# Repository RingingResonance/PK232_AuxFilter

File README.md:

# PK232_AuxFilter
An added filter stage for the PK232's packet modem descriminator based on the same circuit's existing filter design.

I don't have the best understanding of how this type of filter works so I copied that part of the schematic resistor-per-resistor
with the goal of helping the PK232 perform a little better when the incoming signal isn't full-quieting. Obviously this is for
models that don't have the DSP filter. This filter should be able to be used for other things by changing the resistor and capacitor
values to fit your needs. It would probably work on other TNC's.

Current resistor and capacitor values for Mark/Space:
VHF mode: 1200/2400 hz
HF mode: 2110/2310 hz

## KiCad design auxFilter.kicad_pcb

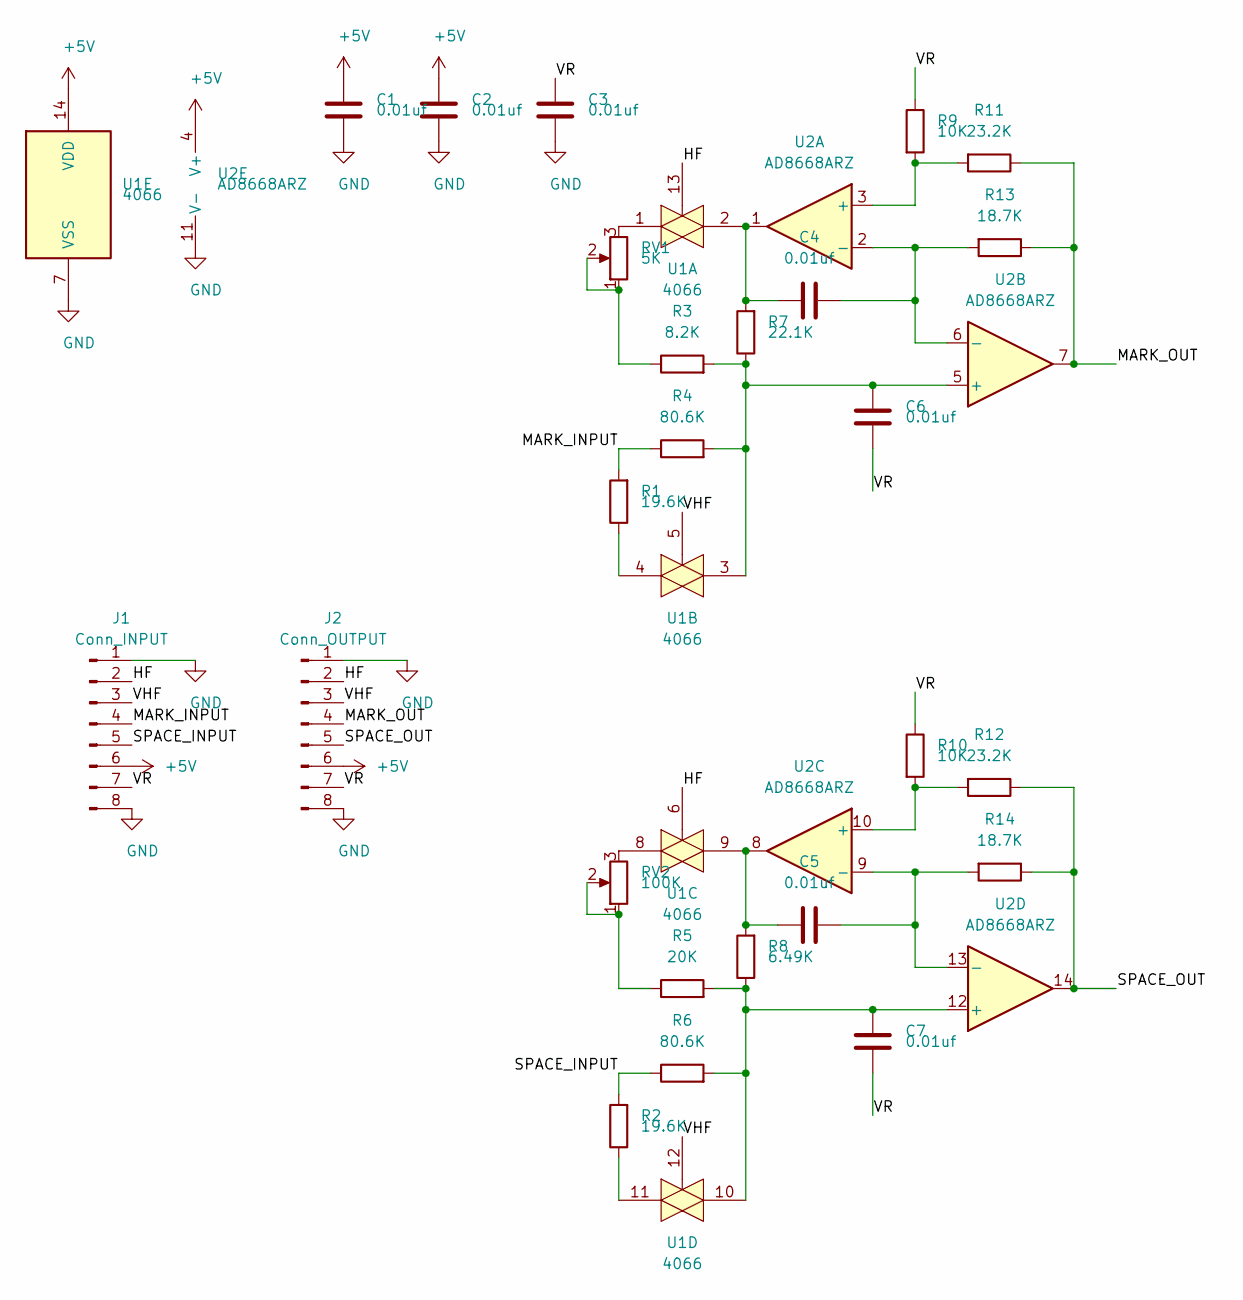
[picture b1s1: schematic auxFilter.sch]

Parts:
C1, C2, C3, C4, C5, C6, C7: 0.01uf; C_0603_HandSoldering; digikey 399-17568-1-ND
J1: Conn_INPUT; Pin_Header_Straight_1x08_Pitch2.54mm
J2: Conn_OUTPUT; Pin_Header_Straight_1x08_Pitch2.54mm
R1, R2: 19.6K; R_0603_HandSoldering; digikey 311-19.6KHRCT-ND
R3: 8.2K; R_0603_HandSoldering; digikey 311-8.2KGRCT-ND
R4, R6: 80.6K; R_0603_HandSoldering; digikey 311-80.6KHRCT-ND
R5: 20K; R_0603_HandSoldering; digikey 13-RC0603FR-1320KLCT-ND
R7: 22.1K; R_0603_HandSoldering; digikey 311-22.1KHRCT-ND
R8: 6.49K; R_0603_HandSoldering; digikey 311-6.49KHRCT-ND
R9, R10: 10K; R_0603_HandSoldering; digikey RNCP0603FTD10K0CT-ND
R11, R12: 23.2K; R_0603_HandSoldering; digikey 311-23.2KHRCT-ND
R13, R14: 18.7K; R_0603_HandSoldering; digikey 311-18.7KHRCT-ND
RV1: 5K; Potentiometer_Trimmer_Vishay_TS53YJ; digikey 3314J-502ECT-ND
RV2: 100K; Potentiometer_Trimmer_Vishay_TS53YJ; digikey 563-ST4ETA104CT-ND
U1: 4066; SOIC-14_3.9x8.7mm_Pitch1.27mm; digikey MC14066BDR2GOSCT-ND
U2: AD8668ARZ; SOIC-14_3.9x8.7mm_Pitch1.27mm; digikey 505-AD8668ARZ-ND

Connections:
+5V: C1.1, C2.1, J1.6, J2.6, U1.14 (VDD), U2.4 (V+)
/HF: J1.2, J2.2, U1.6, U1.13
/MARK_INPUT: J1.4, R1.2, R4.1
/MARK_OUT: J2.4, R11.1, R13.1, U2.7
/SPACE_INPUT: J1.5, R2.2, R6.1
/SPACE_OUT: J2.5, R12.1, R14.1, U2.14
/VHF: J1.3, J2.3, U1.5, U1.12
/VR: C3.1, C6.2, C7.2, J1.7, J2.7, R9.1, R10.1
GND: C1.2, C2.2, C3.2, J1.1, J1.8, J2.1, J2.8, U1.7 (VSS), U2.11 (V-)
unnamed: C4.1, R13.2, U2.2 (-), U2.6 (-)
unnamed: C4.2, R7.2, U1.2, U2.1
unnamed: C5.1, R14.2, U2.9 (-), U2.13 (-)
unnamed: C5.2, R8.2, U1.9, U2.8
unnamed: C6.1, R3.2, R4.2, R7.1, U1.3, U2.5 (+)
unnamed: C7.1, R5.2, R6.2, R8.1, U1.10, U2.12 (+)
unnamed: R1.1, U1.4
unnamed: R2.1, U1.11
unnamed: R3.1, RV1.1, RV1.2
unnamed: R5.1, RV2.1, RV2.2
unnamed: R10.2, R12.2, U2.10 (+)
unnamed: R9.2, R11.2, U2.3 (+)
unnamed: RV1.3, U1.1
unnamed: RV2.3, U1.8

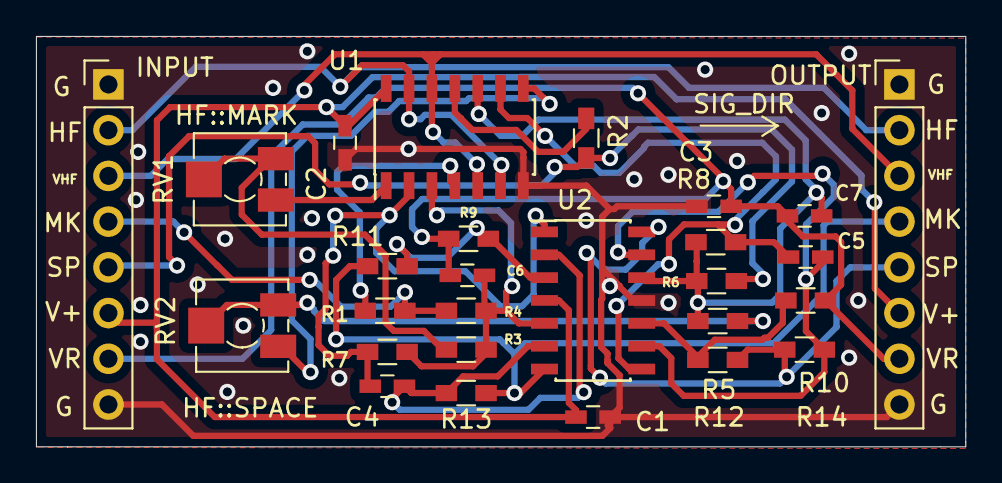
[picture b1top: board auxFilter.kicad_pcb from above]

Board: 2 copper layers, 51.6 x 22.8 mm, 27 parts (0 on the bottom side), 23 nets.

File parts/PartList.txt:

7: 0.01uF 0603 capacitor :: 399-17568-1-ND

2: 19.6K 0603 resistor :: 311-19.6KHRCT-ND

1: 8.2K 0603 resistor :: 311-8.2KGRCT-ND

2: 80.6K 0603 resistor :: 311-80.6KHRCT-ND

1: 20K 0603 resistor :: 13-RC0603FR-1320KLCT-ND

1: 22.1K 0603 resistor :: 311-22.1KHRCT-ND

1: 6.49K 0603 resistor :: 311-6.49KHRCT-ND

2: 10K 0603 resistor :: RNCP0603FTD10K0CT-ND

2: 23.2K 0603 resistor :: 311-23.2KHRCT-ND

2: 18.7K 0603 resistor :: 311-18.7KHRCT-ND

1: 5K 0603 resistor :: 3314J-502ECT-ND

1: 100K 0603 resistor :: 563-ST4ETA104CT-ND

1: Analog Switch SOIC 74HC4066D :: 1727-2811-1-ND

1: Quad Op-Amp SOIC AD8668ARZ :: 505-AD8668ARZ-ND

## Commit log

2023-08-09 Added PDF schematic.
2023-08-09 Added board rendering.
2023-08-24 Added some new images. Changed analog switch part No to one that can handle more than 5v.
